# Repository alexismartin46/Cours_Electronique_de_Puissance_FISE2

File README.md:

# <u>ENSEA</u> : Cours Electronique de Puissance FISE2

Module enseigné en Français et Anglais à l'ENSEA : Ecole Nationale Supérieure de l'Electronique et de ses Applications. 2ème année Formation Ingénieur (M1)
Le cours porte sur les convertisseurs DC/DC.

Volume horaire :
- Cours : 8 x 2h = 16h
- TD : 9 x 2h = 18h
- TP : 4 x 4h = 16h

## Cours
Sources uniquement en anglais

- Alimentations DC/DC non isolées : Buck, Boost, 2Q, 4Q, Buck/Boost, Cück, SEPIC
- Alimentations DC/DC isolées : Flyback, Forward, Push-Pull
- Composants de puissance : Inductances, Condensateurs, Diodes (Schottky, Zener, TVS), polyfuse
- Correction du Facteur de puissance (PFC)

## TDs
Sujets et correction en anglais et français

- Buck
- Boost
- Bras de pont
- Onduleur monophasé
- Hacheur 4 quadrants
- Flyback
- Forward Asymétrique

## TPs
Sujets en anglais et français

- Buck (LTSpice)
- Hacheur 4 quadrants + MCC
- Flyback
- Forward

## TP_Buck_LT1959
Maquette de TP "Buck" autour du LT1959 (Analog Device). PCB réalisé avec KiCAD

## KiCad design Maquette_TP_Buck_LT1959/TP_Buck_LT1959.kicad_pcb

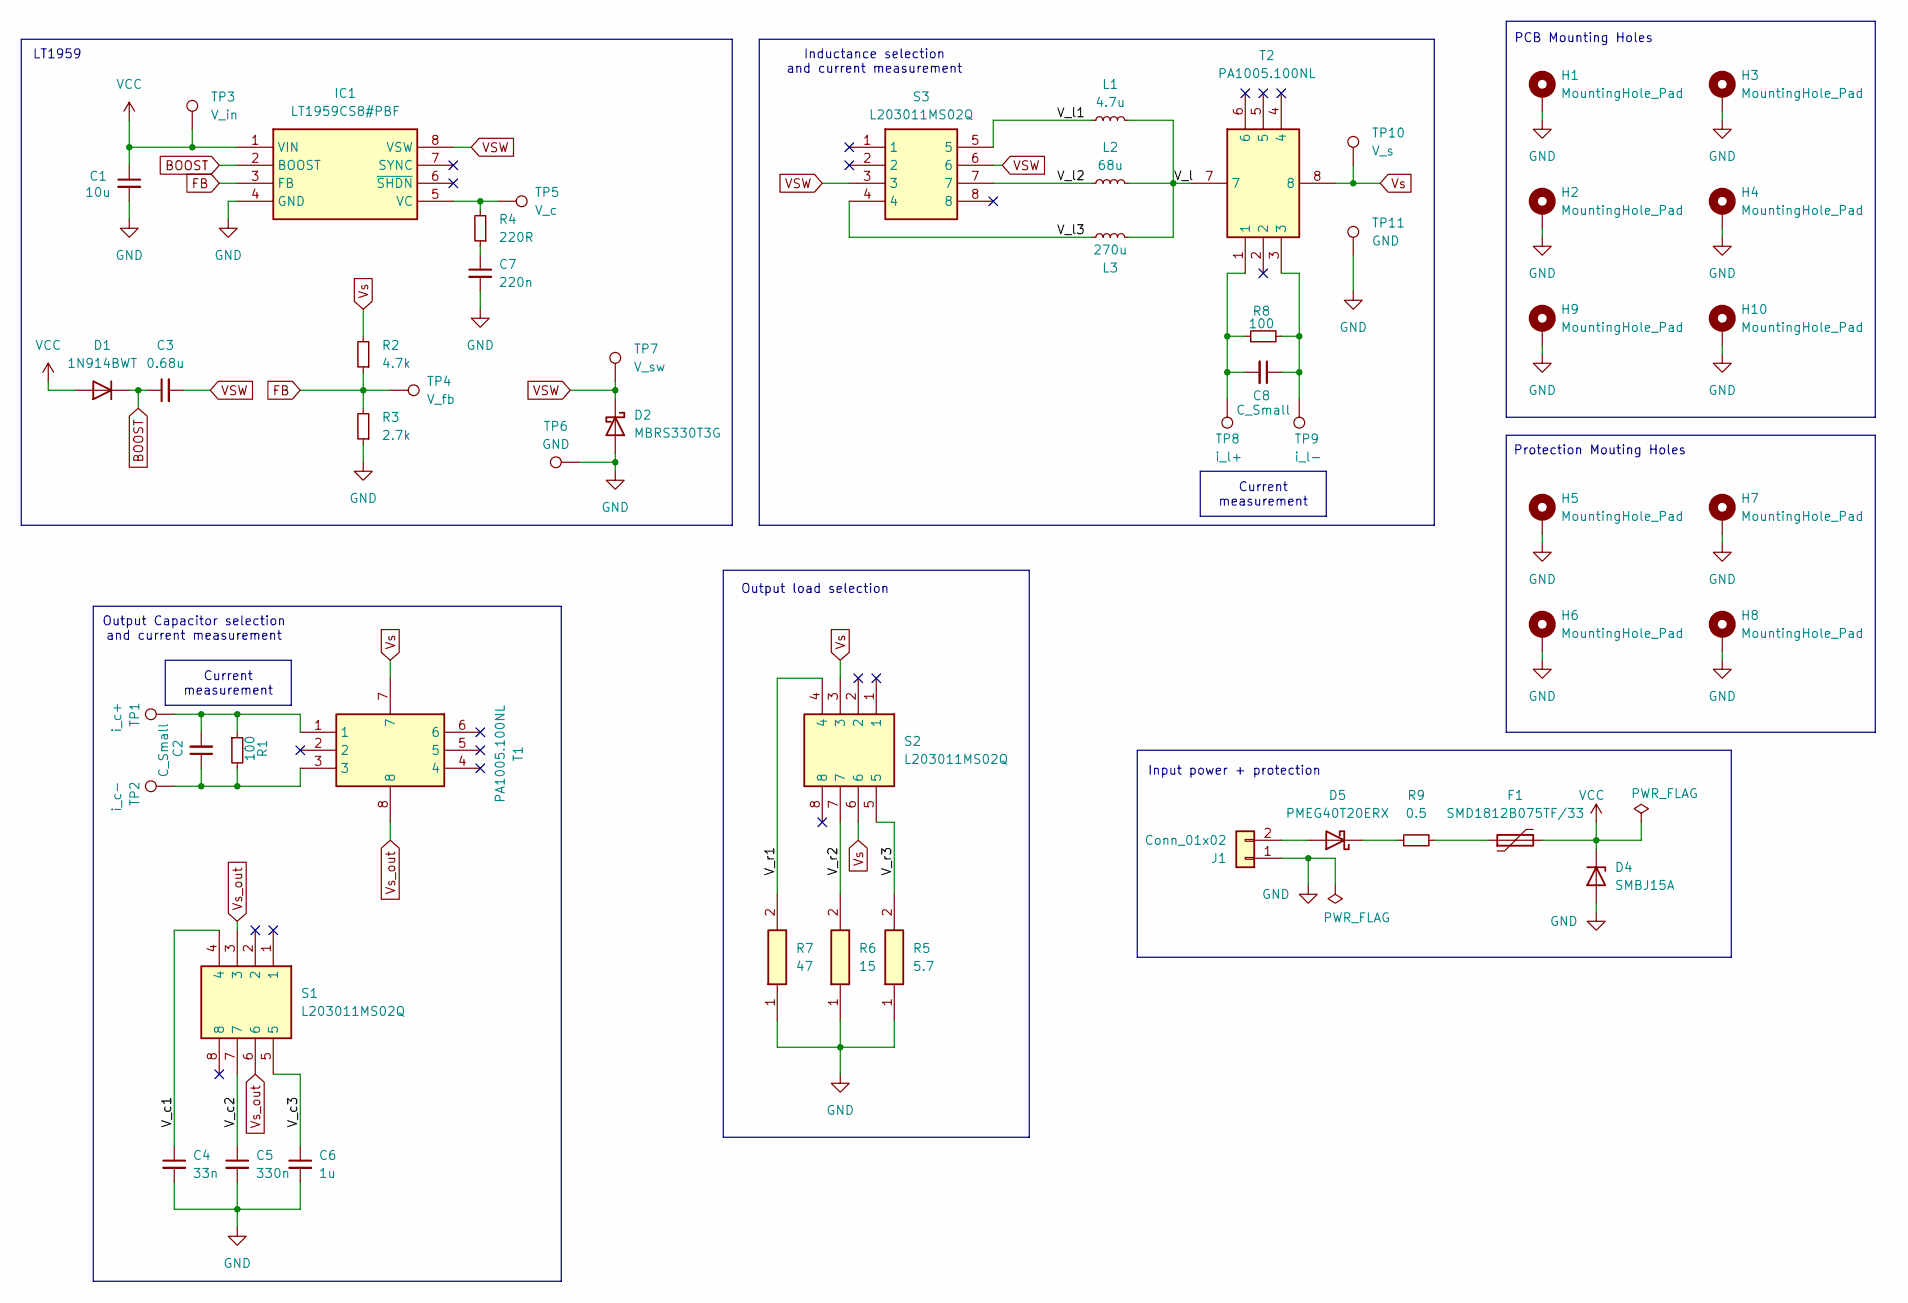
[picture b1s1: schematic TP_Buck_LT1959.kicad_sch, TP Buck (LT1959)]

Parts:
C1: 10u; C_0805_2012Metric
C2, C8: C_Small; C_0805_2012Metric
C3: 0.68u; C_0805_2012Metric
C4: 33n; C_0805_2012Metric
C5: 330n; C_0805_2012Metric
C6: 1u; C_0805_2012Metric
C7: 220n; C_0805_2012Metric
D1: 1N914BWT; D_SOD-523
D2: MBRS330T3G; DIOM7958X256N
D4: SMBJ15A; D_SMB_Handsoldering
D5: PMEG40T20ERX; D_SOD-123
F1: SMD1812B075TF/33; FUSC4632X165N
H1, H2, H3, H4, H5, H6, H7, H8, H9, H10: MountingHole_Pad; MountingHole_3.2mm_M3_ISO7380_Pad
IC1: LT1959CS8#PBF; SOIC-8_3.9x4.9mm_P1.27mm; Manufacturer_Part_Number LT1959CS8#PBF; Mouser Part Number 584-LT1959CS8#PBF
J1: Conn_01x02; SHDR2W90P0X508_1X2_1076X1135X1810P
L1: 4.7u; WE-PD_1260_1245_1280_121054
L2: 68u; WE-PD_1260_1245_1280_121054
L3: 270u; WE-PD_1260_1245_1280_121054
R1, R8: 100; R_0805_2012Metric
R2: 4.7k; R_1206_3216Metric
R3: 2.7k; R_1206_3216Metric
R4: 220R; R_1206_3216Metric
R5: 5.7; RESC6432X120N; Manufacturer_Part_Number 352247RFT; Mouser Part Number 279-352247RFT
R6: 15; RESC6432X120N; Manufacturer_Part_Number 352247RFT; Mouser Part Number 279-352247RFT
R7: 47; RESC6432X120N; Manufacturer_Part_Number 352247RFT; Mouser Part Number 279-352247RFT
R9: 0.5; R_1206_3216Metric
S1, S2, S3: L203011MS02Q; Manufacturer_Part_Number L203011MS02Q; Mouser Part Number 611-L203011MS02Q
T1, T2: PA1005.100NL; PA1005100NL; Mouser Part Number 673-PA1005.100NL
TP1: i_c+; 5000
TP2: i_c-; 5000
TP3: V_in; 5000
TP4: V_fb; 5000
TP5: V_c; 5000
TP6, TP11: GND; 5000
TP7: V_sw; 5000
TP8: i_l+; 5000
TP9: i_l-; 5000
TP10: V_s; 5000

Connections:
/V_c1: C4.1, S1.4
/V_c2: C5.1, S1.7
/V_c3: C6.1, S1.5
/V_l: L1.2, L2.2, L3.2, T2.7
/V_l1: L1.1, S3.5
/V_l2: L2.1, S3.7
/V_l3: L3.1, S3.4
/V_r1: R7.2, S2.4
/V_r2: R6.2, S2.7
/V_r3: R5.2, S2.5
BOOST: C3.1, D1.1 (K), IC1.2 (BOOST)
FB: IC1.3 (FB), R2.1, R3.2, TP4.1
GND: C1.2, C4.2, C5.2, C6.2, C7.2, D2.2 (A), D4.2 (A), H1.1, H2.1, H3.1, H4.1, H5.1, H6.1, H7.1, H8.1, H9.1, H10.1, IC1.4 (GND), J1.1, R3.1, R5.1, R6.1, R7.1, TP6.1, TP11.1
unnamed: C2.1, R1.2, T1.3, TP2.1
unnamed: C2.2, R1.1, T1.1, TP1.1
unnamed: C7.1, R4.1
unnamed: C8.1, R8.2, T2.3, TP9.1
unnamed: C8.2, R8.1, T2.1, TP8.1
unnamed: D5.2 (A), J1.2
unnamed: D5.1 (K), R9.1
unnamed: F1.1, R9.2
unnamed: IC1.5 (VC), R4.2, TP5.1
VCC: C1.1, D1.2 (A), D4.1 (K), F1.2, IC1.1 (VIN), TP3.1
VSW: C3.2, D2.1 (K), IC1.8 (VSW), S3.3, S3.6, TP7.1
Vs: R2.2, S2.3, S2.6, T1.7, T2.8, TP10.1
Vs_out: S1.3, S1.6, T1.8

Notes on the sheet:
Output load selection
Protection Mouting Holes
PCB Mounting Holes
Input power + protection
Output Capacitor selection and current measurement
Inductance selection and current measurement
LT1959
Current measurement

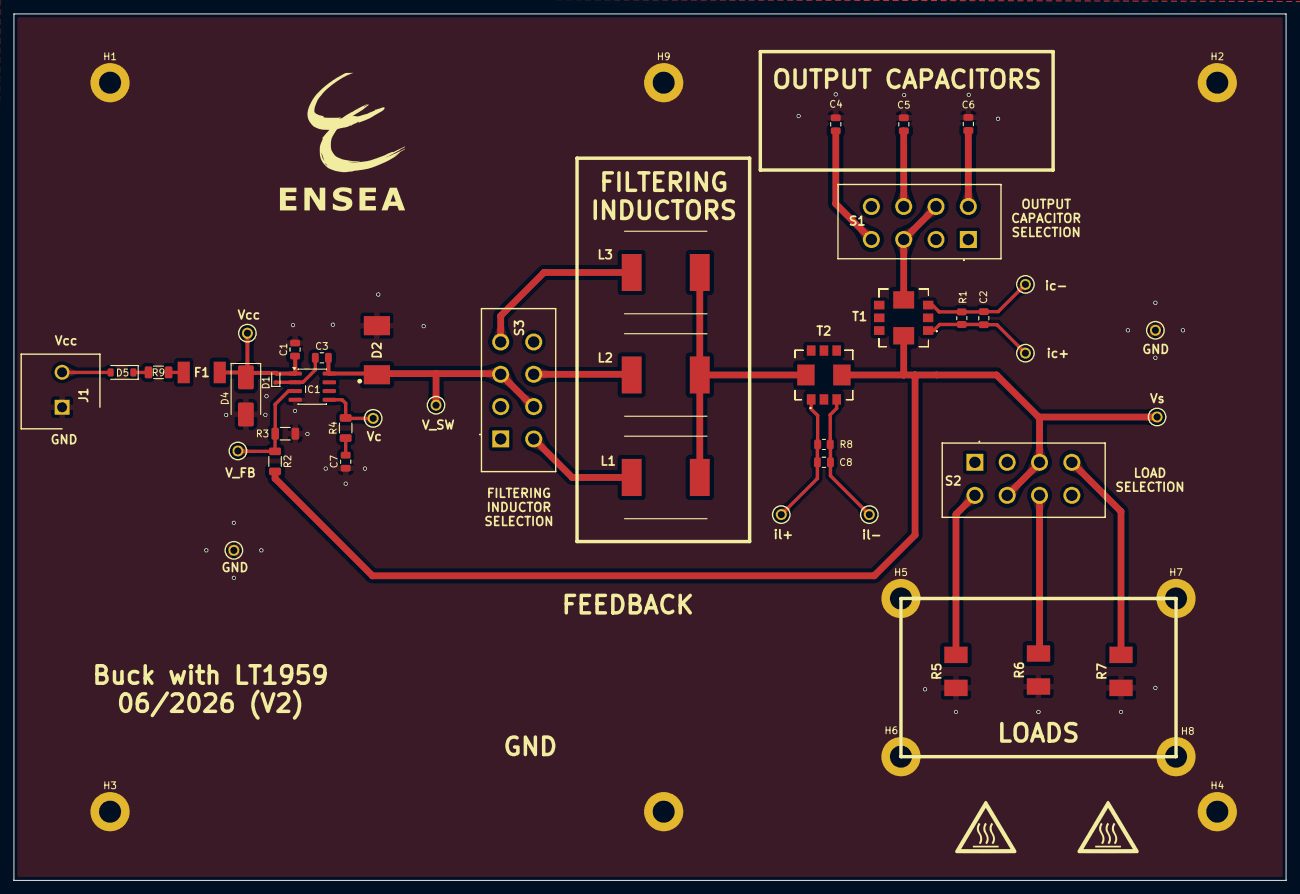
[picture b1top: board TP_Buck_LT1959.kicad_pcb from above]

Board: 2 copper layers, 185.0 x 126.0 mm, 53 parts (0 on the bottom side), 26 nets.

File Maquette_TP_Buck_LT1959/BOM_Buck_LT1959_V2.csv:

Id;RÃ©fÃ©rence;Empreinte;QuantitÃ©;DÃ©signation;Fournisseur et rÃ©f;Prix unitaire (04/04/2026);Remarques
20;C1;C_0805_2012Metric;1;10u;Wurth;;
10;C3;C_0805_2012Metric;1;0.68u;Wurth;;
25;C4;C_0805_2012Metric;1;33n;Wurth;;
21;C5;C_0805_2012Metric;1;330n;Wurth;;
36;C6;C_0805_2012Metric;1;1u;Wurth;;
30;C7;C_0805_2012Metric;1;220n;Wurth;;
14;C8,C2;C_0805_2012Metric;2;C_Small;Wurth;;emplacement si nécessaire, ne pas souder dans la version actuelle
15;D1;D_SOD-523;1;1N914BWT;RS;0,031;
3;D2;DIOM7958X256N;1;MBRS330T3G;RS;;
27;D4;D_SMB_Handsoldering;1;SMBJ15A;Mouser;0,282;
17;D5;D_SOD-123;1;PMEG40T20ERX;Mouser;0,097;
37;F1;FUSC4632X165N;1;SMD1812B075TF/33;Mouser;0,147;
35;IC1;SOIC-8_3.9x4.9mm_P1.27mm;1;LT1959CS8#PBF;Mouser;9,98;
16;J1;SHDR2W90P0X508_1X2_1076X1135X1810P;1;Conn_01x02;Wurth;;
33;L1;WE-PD_1260_1245_1280_121054;1;4.7u;Wurth;;
26;L2;WE-PD_1260_1245_1280_121054;1;68u;Wurth;;
34;L3;WE-PD_1260_1245_1280_121054;1;680u;Wurth;;
8;R2;R_1206_3216Metric;1;4.7k;Wurth;;
28;R3;R_1206_3216Metric;1;2.7k;Wurth;;
4;R4;R_1206_3216Metric;1;220R;Wurth;;
2;R5;RESC6432X120N;1;5.7;Farnell;0,49;
6;R6;RESC6432X120N;1;15;Farnell;0,48;
24;R7;RESC6432X120N;1;47;Farnell;0,497;
13;R8,R1;R_0805_2012Metric;2;100;Wurth;;
19;R9;R_1206_3216Metric;1;0.5;Wurth;;
7;S2,S3,S1;L203011MS02Q;3;L203011MS02Q;Mouser;3,6;
5;T1,T2;PA1005100NL;2;PA1005.100NL;Mouser;1,38;
32;TP1;5000;1;i_c+;RS;0,184;blanc
22;TP10;5000;1;V_s;RS;0,184;rouge
31;TP2;5000;1;i_c-;RS;0,183;noir
9;TP3;5000;1;V_in;RS;0,184;blanc
11;TP4;5000;1;V_fb;RS;0,184;rouge
1;TP5;5000;1;V_c;RS;0,184;vert
12;TP6,TP11;5000;2;GND;RS;0,184;vert
29;TP7;5000;1;V_sw;RS;0,184;vert
23;TP8;5000;1;i_l+;RS;0,184;blanc
18;TP9;5000;1;i_l-;RS;0,184;blanc

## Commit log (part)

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2026-04-08 gitignore
2026-04-09 update cours 1
2026-05-06 TD 1 et 2 Update
2026-05-28 test update
2026-06-02 Ajout Maquette TP + Update Cours
2026-06-04 Update Cours composants
2026-06-19 update PCB Buck et TD
2026-06-19 update README PCB Buck
2026-06-22 Update TP
2026-06-22 Clean files
2026-06-22 Update TD
2026-06-24 Update Cours
2026-06-25 Update TDs
2026-06-29 Add TD Buck with AI
2026-06-29 Update Cours et TD Buck avec IA
2026-06-29 Update nom de dossier
2026-06-30 Update TD Buck IA
